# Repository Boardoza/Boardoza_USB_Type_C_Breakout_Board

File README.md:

# Boardoza USB Type-C USB 2.0 Breakout Board

The **Boardoza USB Type-C Breakout Board** is a simple adapter board for a **USB Type-C connector**. It converts the small surface-mount pins of the USB Type-C connector into standard **2.54 mm through-hole pins**, making the connector easier to use with development boards, breadboards, and custom electronics projects.

It supports **USB 2.0** connections and can be used for USB Type-C prototyping, power connections, data communication, and testing without having to solder directly to the small pins of a USB Type-C connector.

|Front Side|Back Side|
|:---:|:---:|
|||

---

## Key Features

- **Easy USB Type-C Connection:** Converts the small USB Type-C connector pins into easy-to-use **2.54 mm through-hole pins**.
- **USB 2.0 Support:** Provides access to **D+** and **D-** pins for USB 2.0 data communication.
- **CC Pin Access:** Provides access to **CC1** and **CC2** pins for USB Type-C connection and cable detection.
- **SB Pin Access:** Provides access to **SB1** and **SB2** pins for projects that require alternate modes.
- **Power Connections:** Provides easy access to **VBUS** and **GND** pins for USB power connections.
- **Easy Prototyping:** Makes the USB Type-C connector easier to use with breadboards, development boards, and custom electronic projects.

---

## Technical Specifications

**Model:** USB Type C  
**Manufacturer:** Boardoza   
**Connector Type:** USB Type-C Receptacle  
**Connector Pin Count:** 16  
**Interface:** USB 2.0  
**Functions:** USB Type-C SMD-to-THT Breakout  
**Operating Temperature:** -40°C to +85°C  
**Board Dimensions:** 20mm x 20mm

---

## Board Pinout

### ( J2 ) USB Data, Configuration & Sideband Pins

| Pin Number | Pin Name | Description |
| :---: | :---: | --- |
| 1, 2 | CC2 | USB Type-C Configuration Channel 2 for cable orientation and connection detection |
| 3, 4 | SB1 | USB Type-C Sideband Use 1 Signal |
| 5, 6 | D+ | USB 2.0 Positive Differential Data Line |
| 7, 8 | D- | USB 2.0 Negative Differential Data Line |
| 9, 10 | CC1 | USB Type-C Configuration Channel 1 for cable orientation and connection detection |
| 11, 12 | SB2 | USB Type-C Sideband Use 2 Signal |

### ( J3 ) USB Power Pins

| Pin Number | Pin Name | Description |
| :---: | :---: | --- |
| 1, 2 | VBUS | USB Bus Power Supply Rail |
| 3, 4 | GND | Ground Reference |

### ( J4 ) USB Power Extension Pins

| Pin Number | Pin Name | Description |
| :---: | :---: | --- |
| 1, 2 | VBUS | USB Bus Power Supply Rail |
| 3, 4 | GND | Ground Reference |

---

## Board Dimensions

---

## Step Files

[Boardoza USB Type C.step](./assets/USB_TYPE_C%20Step.step)

---

## Sensor Datasheet

[USB Type-C User Manual.pdf](./assets/USB_TYPE_C%20User%20Manual.pdf)

---

## Version History

- V1.0.0 - Initial Release

---

## Support

- If you have any questions or need support, please contact <support@boardoza.com>

---

## **License**
### **Hardware Design**

[![CC BY-SA 4.0][cc-by-sa-shield]][cc-by-sa]

All hardware design files are licensed under [Creative Commons Attribution-ShareAlike 4.0 International License][cc-by-sa].

[cc-by-sa]: http://creativecommons.org/licenses/by-sa/4.0/
[cc-by-sa-shield]: https://img.shields.io/badge/License-CC%20BY--SA%204.0-lightgrey.svg

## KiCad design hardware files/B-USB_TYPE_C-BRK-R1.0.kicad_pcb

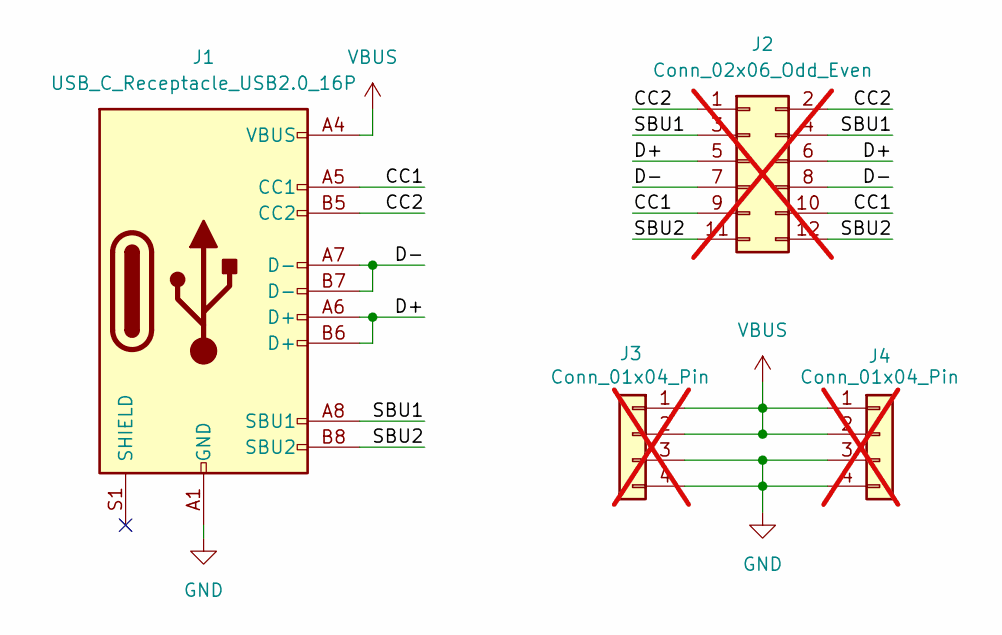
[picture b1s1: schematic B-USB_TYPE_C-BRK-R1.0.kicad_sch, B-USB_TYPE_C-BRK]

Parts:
J1: USB_C_Receptacle_USB2.0_16P; USB_C_Receptacle_GCT_USB4105-xx-A_16P_TopMnt_Horizontal; MPN L-KLS1-5416-L2-01-R
J2: Conn_02x06_Odd_Even; PinHeader_2x06_P2.54mm_Vertical; MPN L-KLS1-207-2.5-2-12-S; not fitted
J3, J4: Conn_01x04_Pin; PinHeader_1x04_P2.54mm_Vertical; MPN L-KLS1-207-1-04-S-2.5X5.; not fitted

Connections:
/CC1: J1.A5 (CC1), J2.9, J2.10
/CC2: J1.B5 (CC2), J2.1, J2.2
/D+: J1.A6 (D+), J1.B6 (D+), J2.5, J2.6
/D-: J1.A7 (D-), J1.B7 (D-), J2.7, J2.8
/SBU1: J1.A8 (SBU1), J2.3, J2.4
/SBU2: J1.B8 (SBU2), J2.11, J2.12
GND: J1.A1 (GND), J1.A12 (GND), J1.B1 (GND), J1.B12 (GND), J3.3, J3.4, J4.3, J4.4
VBUS: J1.A4 (VBUS), J1.A9 (VBUS), J1.B4 (VBUS), J1.B9 (VBUS), J3.1, J3.2, J4.1, J4.2

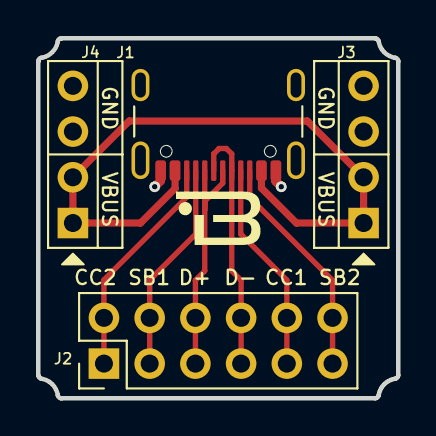
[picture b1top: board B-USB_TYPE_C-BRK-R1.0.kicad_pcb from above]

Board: 2 copper layers, 20.0 x 20.0 mm, 4 parts (0 on the bottom side), 8 nets.
